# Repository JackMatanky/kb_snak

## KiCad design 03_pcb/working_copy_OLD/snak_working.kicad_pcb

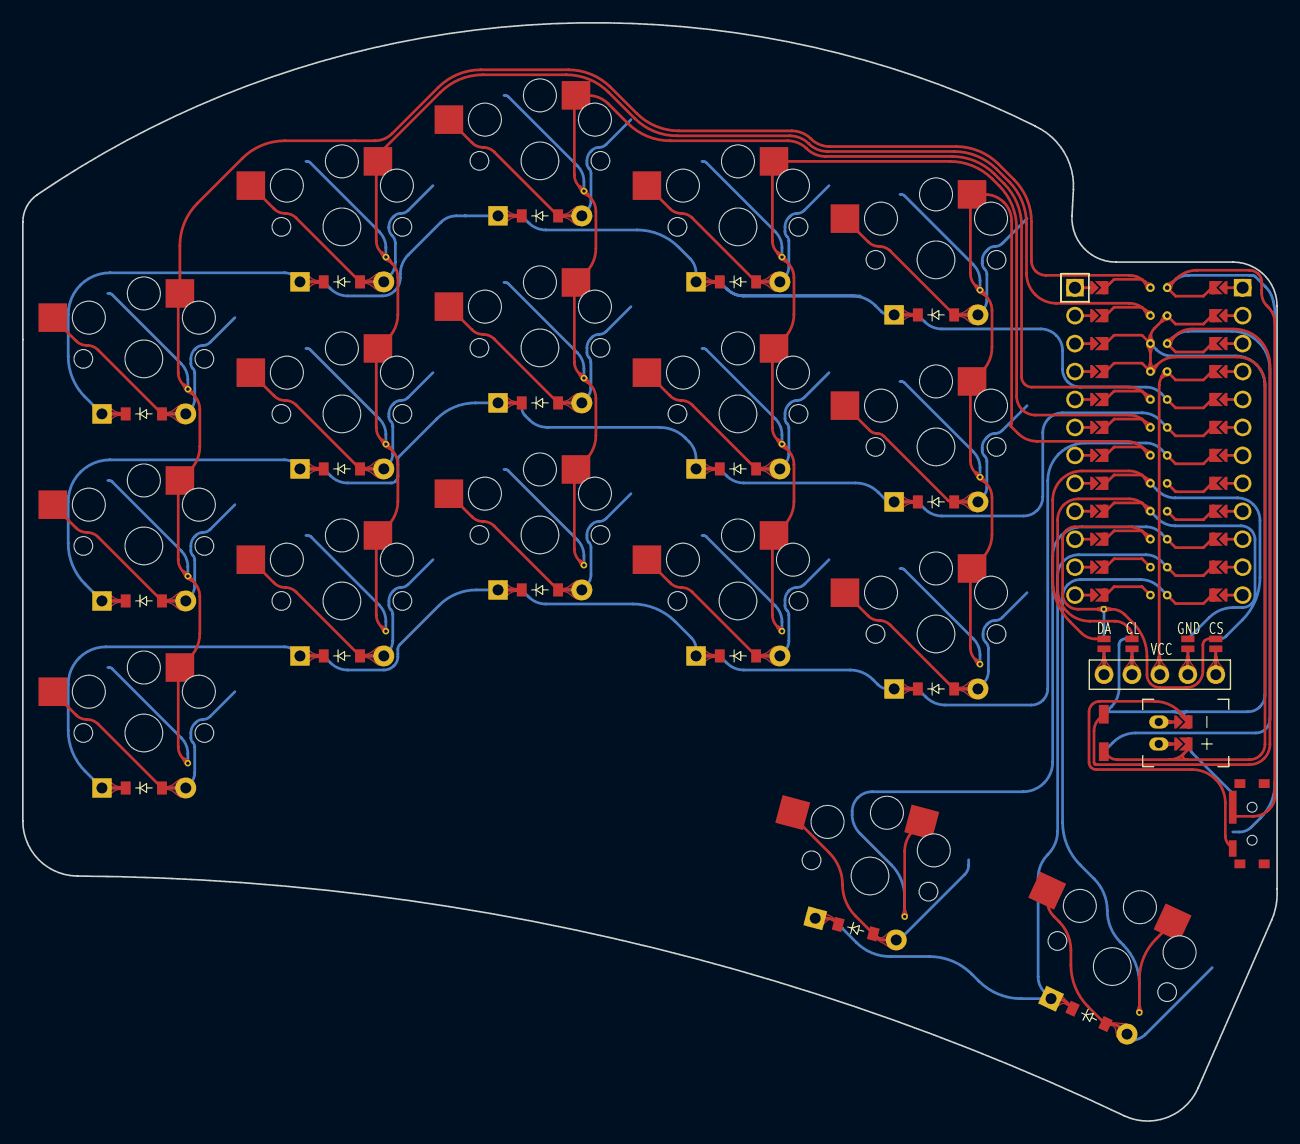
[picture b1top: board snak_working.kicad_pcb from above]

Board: 2 copper layers, 114.0 x 99.8 mm, 37 parts (0 on the bottom side), 39 nets.

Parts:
D1, D2, D3, D4, D5, D6, D7, D8, D9, D10, D11, D12, D13, D14, D15, D16, D17: ComboDiode
DISP1: nice!view
JST1: JST_PH_S2B-PH-K
MCU1: ProMicro
S1, S2, S3, S4, S5, S6, S7, S8, S9, S10, S11, S12, S13, S14, S15, S16, S17: PG1350

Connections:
DISP1_1: DISP1.1, DISP1.10, DISP1.23
DISP1_2: DISP1.2, DISP1.11, DISP1.22
DISP1_4: DISP1.4, DISP1.12, DISP1.21
DISP1_5: DISP1.5, DISP1.13, DISP1.20
GND: DISP1.16, DISP1.26, JST1.1, MCU1.2, MCU1.21, MCU1.22
JST1_1: JST1.11, JST1.21, JST1.31
JST1_2: JST1.12, JST1.22, JST1.32
P0: MCU1.23, S4.1, S5.1, S6.1
P1: MCU1.24, S1.1, S2.1, S3.1
P2: MCU1.20, S7.1, S8.1, S9.1
P3: MCU1.19, S10.1, S11.1, S12.1
P4: MCU1.18, S13.1, S14.1, S15.1
P5: DISP1.14, DISP1.24, MCU1.17
P6: DISP1.15, DISP1.25, MCU1.16
P7: DISP1.17, DISP1.27, MCU1.15
P10: MCU1.12, S17.1
P14: MCU1.10, S16.1
P16: D16.1, D17.1, MCU1.11
P19: D1.1, D4.1, D7.1, D10.1, D13.1, MCU1.7
P20: D2.1, D5.1, D8.1, D11.1, D14.1, MCU1.6
P21: D3.1, D6.1, D9.1, D12.1, D15.1, MCU1.5
VCC: DISP1.3, MCU1.4
in_home: D17.2, S17.2
index_bot: D10.2, S10.2
index_mid: D11.2, S11.2
index_top: D12.2, S12.2
inner_bot: D13.2, S13.2
inner_mid: D14.2, S14.2
inner_top: D15.2, S15.2
middle_bot: D7.2, S7.2
middle_mid: D8.2, S8.2
middle_top: D9.2, S9.2
out_home: D16.2, S16.2
pinky_bot: D1.2, S1.2
pinky_mid: D2.2, S2.2
pinky_top: D3.2, S3.2
ring_bot: D4.2, S4.2
ring_mid: D5.2, S5.2
ring_top: D6.2, S6.2

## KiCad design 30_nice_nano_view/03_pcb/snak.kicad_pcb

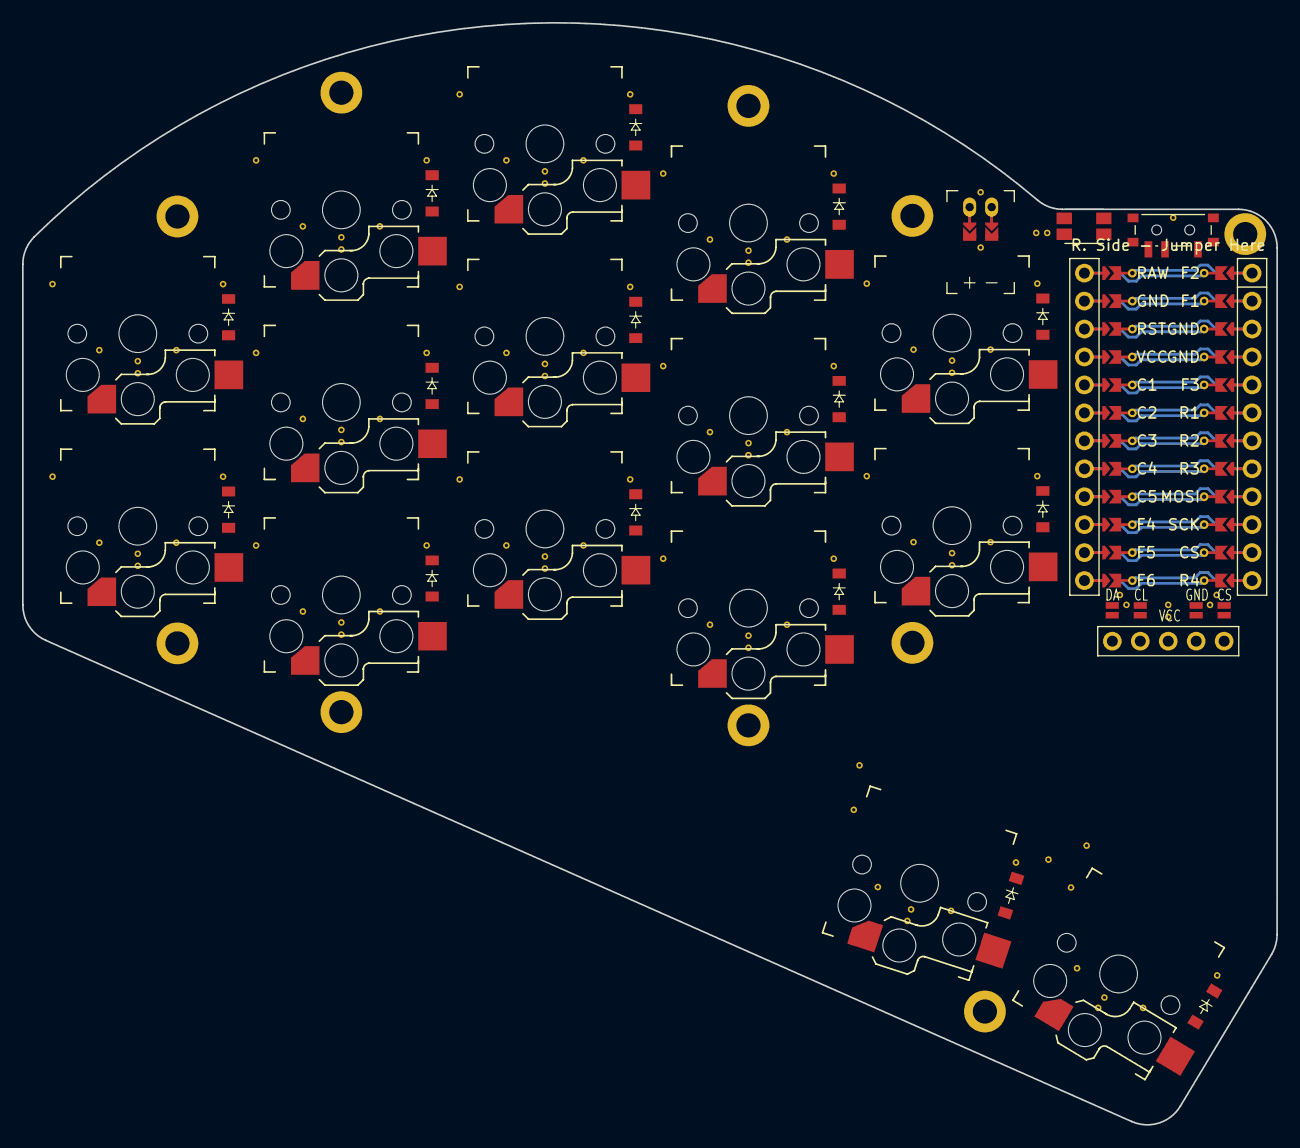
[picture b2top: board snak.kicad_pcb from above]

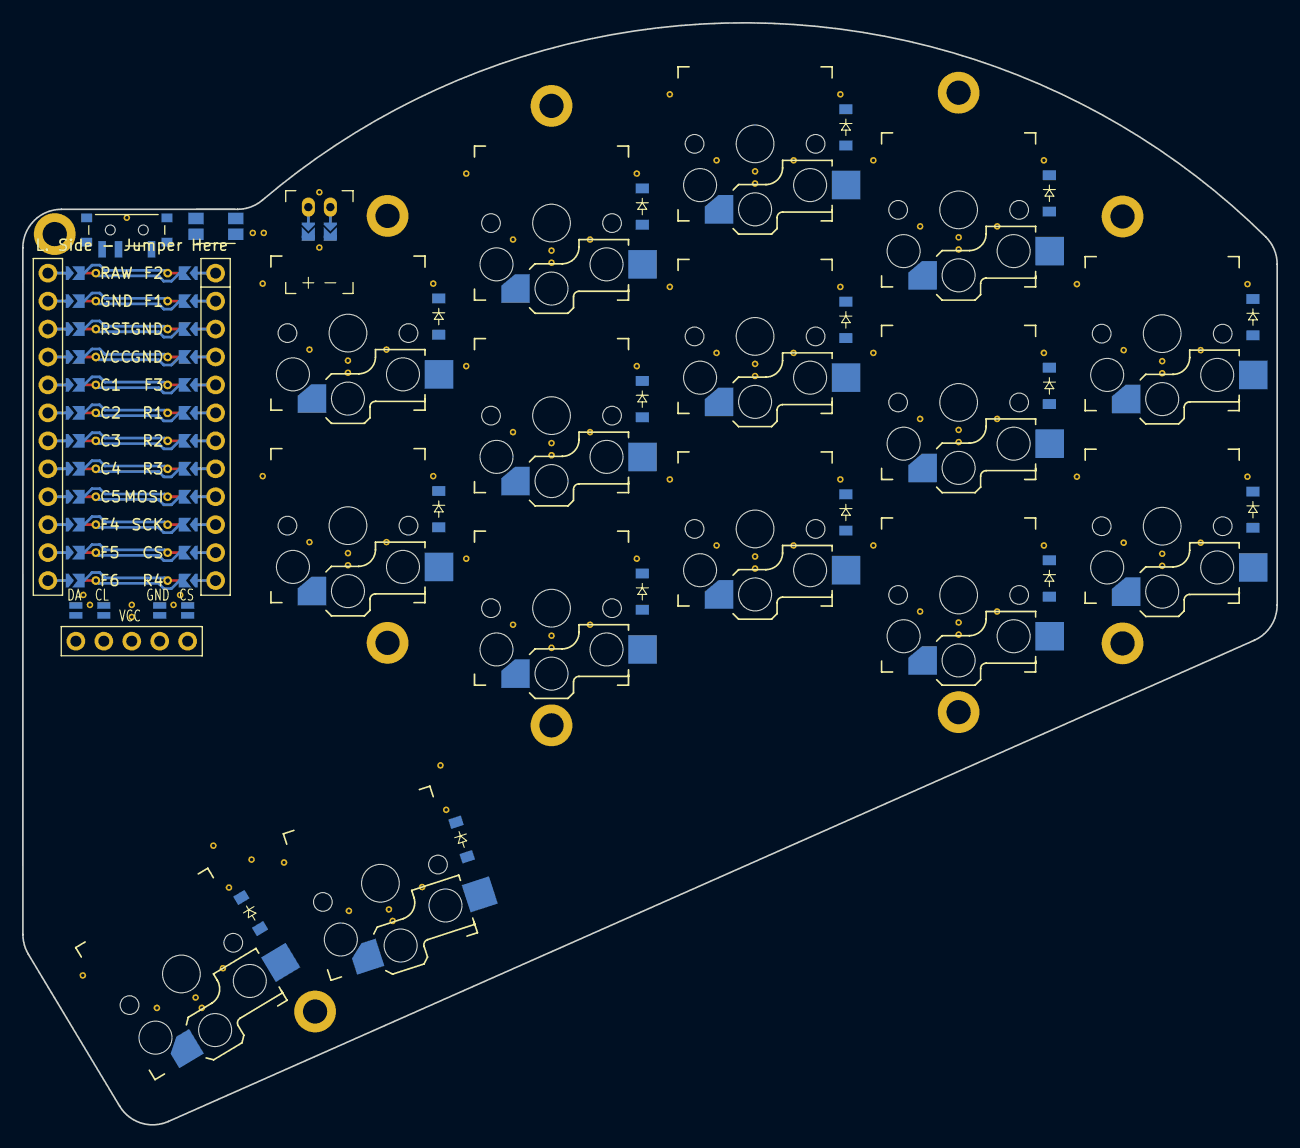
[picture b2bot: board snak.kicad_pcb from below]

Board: 2 copper layers, 114.0 x 100.2 mm, 60 parts (15 on the bottom side), 38 nets.

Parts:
D1, D2, D3, D4, D5, D6, D7, D8, D9, D10, D11, D12, D13, D14, D15, D16, D17, D18, D19, D20, D21, D22, D23, D24, D25, D26, D27, D28, D29, D30: diode_tht_sod123
DISP1: nice!view
H1, H2, H3, H4, H5, H6, H7, H8, H9, H10: mounting_hole
JST1: JST_PH_S2B-PH-K
MCU1: nice_nano
S1, S2, S3, S4, S5, S6, S7, S8, S9, S10, S11, S12, S13, S14, S15: PG1350
SW1: power_switch
SW2: sw_reset_side

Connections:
C1: MCU1.5, S1.1, S2.1
C2: MCU1.6, S3.1, S4.1, S5.1
C3: MCU1.7, S6.1, S7.1, S8.1
C4: MCU1.8, S9.1, S10.1, S11.1, S14.1
C5: MCU1.9, S12.1, S13.1, S15.1
CS: DISP1.17, DISP1.27, MCU1.114
DISP1_1: DISP1.1, DISP1.10, DISP1.23
DISP1_2: DISP1.2, DISP1.11, DISP1.22
DISP1_4: DISP1.4, DISP1.12, DISP1.21
DISP1_5: DISP1.5, DISP1.13, DISP1.20
GND: DISP1.16, DISP1.26, JST1.1, MCU1.2, MCU1.121, MCU1.122, SW2.1
JST1_1: JST1.11, JST1.21, JST1.31
JST1_2: JST1.12, JST1.22, JST1.32
MOSI: DISP1.14, DISP1.24, MCU1.116
R1: D2.1, D5.1, D8.1, D11.1, D13.1, D17.1, D20.1, D23.1, D26.1, D28.1, MCU1.119
R2: D1.1, D4.1, D7.1, D10.1, D12.1, D16.1, D19.1, D22.1, D25.1, D27.1, MCU1.118
R3: D3.1, D6.1, D9.1, D18.1, D21.1, D24.1, MCU1.117
R4: D14.1, D15.1, D29.1, D30.1, MCU1.113
RAW: MCU1.1, SW1.3, SW1.6
RST: MCU1.3, SW2.2
SCK: DISP1.15, DISP1.25, MCU1.115
VCC: DISP1.3, MCU1.4
in_home: D15.2, D30.2, S15.2
index_bot: D9.2, D24.2, S9.2
index_mid: D10.2, D25.2, S10.2
index_top: D11.2, D26.2, S11.2
inner_mid: D12.2, D27.2, S12.2
inner_top: D13.2, D28.2, S13.2
middle_bot: D6.2, D21.2, S6.2
middle_mid: D7.2, D22.2, S7.2
middle_top: D8.2, D23.2, S8.2
out_home: D14.2, D29.2, S14.2
pinky_mid: D1.2, D16.2, S1.2
pinky_top: D2.2, D17.2, S2.2
pos: JST1.2, SW1.2, SW1.5
ring_bot: D3.2, D18.2, S3.2
ring_mid: D4.2, D19.2, S4.2
ring_top: D5.2, D20.2, S5.2

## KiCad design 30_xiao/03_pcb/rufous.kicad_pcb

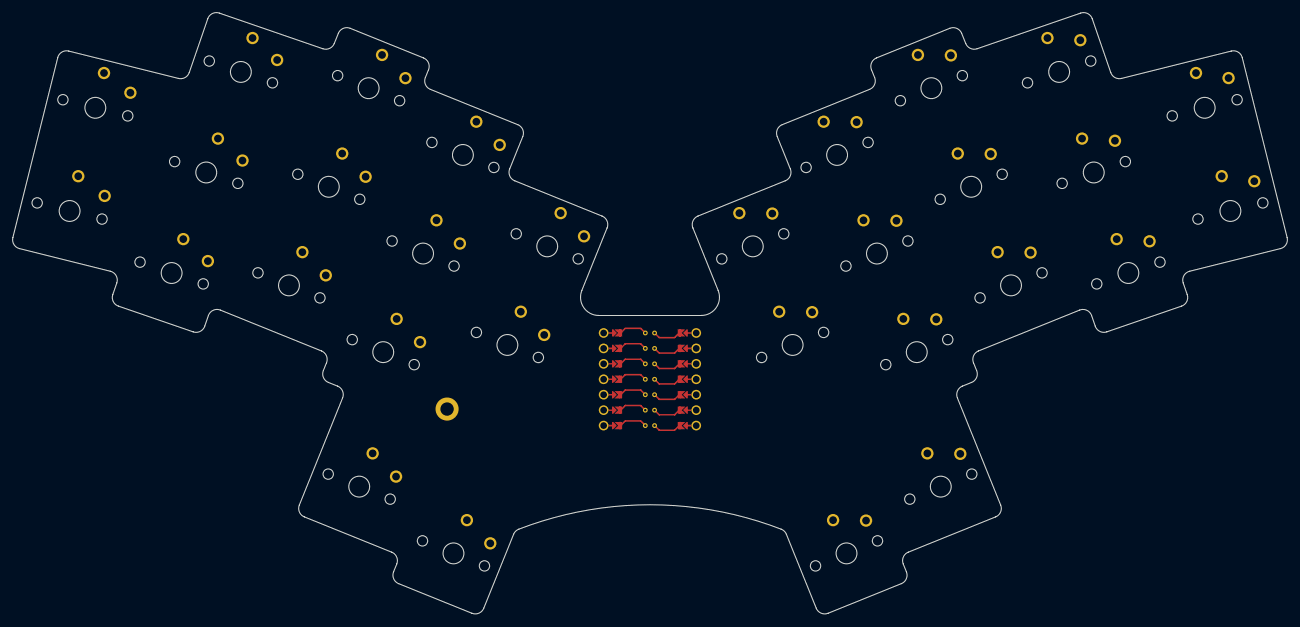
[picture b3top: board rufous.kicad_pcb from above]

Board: 2 copper layers, 209.8 x 99.0 mm, 32 parts (0 on the bottom side), 11 nets, no tracks yet.

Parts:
H1: mounting_hole
S1, S2, S3, S4, S5, S6, S7, S8, S9, S10, S11, S12, S13, S14, S15, S16, S17, S18, S19, S20, S21, S22, S23, S24, S25, S26, S27, S28, S29, S30: PG1350
xiao-ble1: ProMicro; xiao-ble

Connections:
P0: S2.1, S8.1, S13.1, S18.1, S24.1, xiao-ble1.24
P1: S5.1, S11.1, S15.1, S21.1, S26.1, xiao-ble1.23
P2: S1.1, S7.1, S12.1, S17.1, S23.1, xiao-ble1.22
P3: S4.1, S10.1, S14.1, S20.1, S25.1, xiao-ble1.21
P4: S3.1, S9.1, S19.1, S28.1, S29.1, xiao-ble1.20
P5: S6.1, S16.1, S22.1, S27.1, S30.1, xiao-ble1.19
P6: S1.2, S2.2, S3.2, S4.2, S5.2, S6.2, xiao-ble1.18
P7: S7.2, S8.2, S9.2, S10.2, S11.2, S27.2, xiao-ble1.7
P8: S12.2, S13.2, S22.2, S25.2, S26.2, S28.2, xiao-ble1.6
P9: S16.2, S19.2, S20.2, S21.2, S23.2, S24.2, xiao-ble1.5
P10: S14.2, S15.2, S17.2, S18.2, S29.2, S30.2, xiao-ble1.4
